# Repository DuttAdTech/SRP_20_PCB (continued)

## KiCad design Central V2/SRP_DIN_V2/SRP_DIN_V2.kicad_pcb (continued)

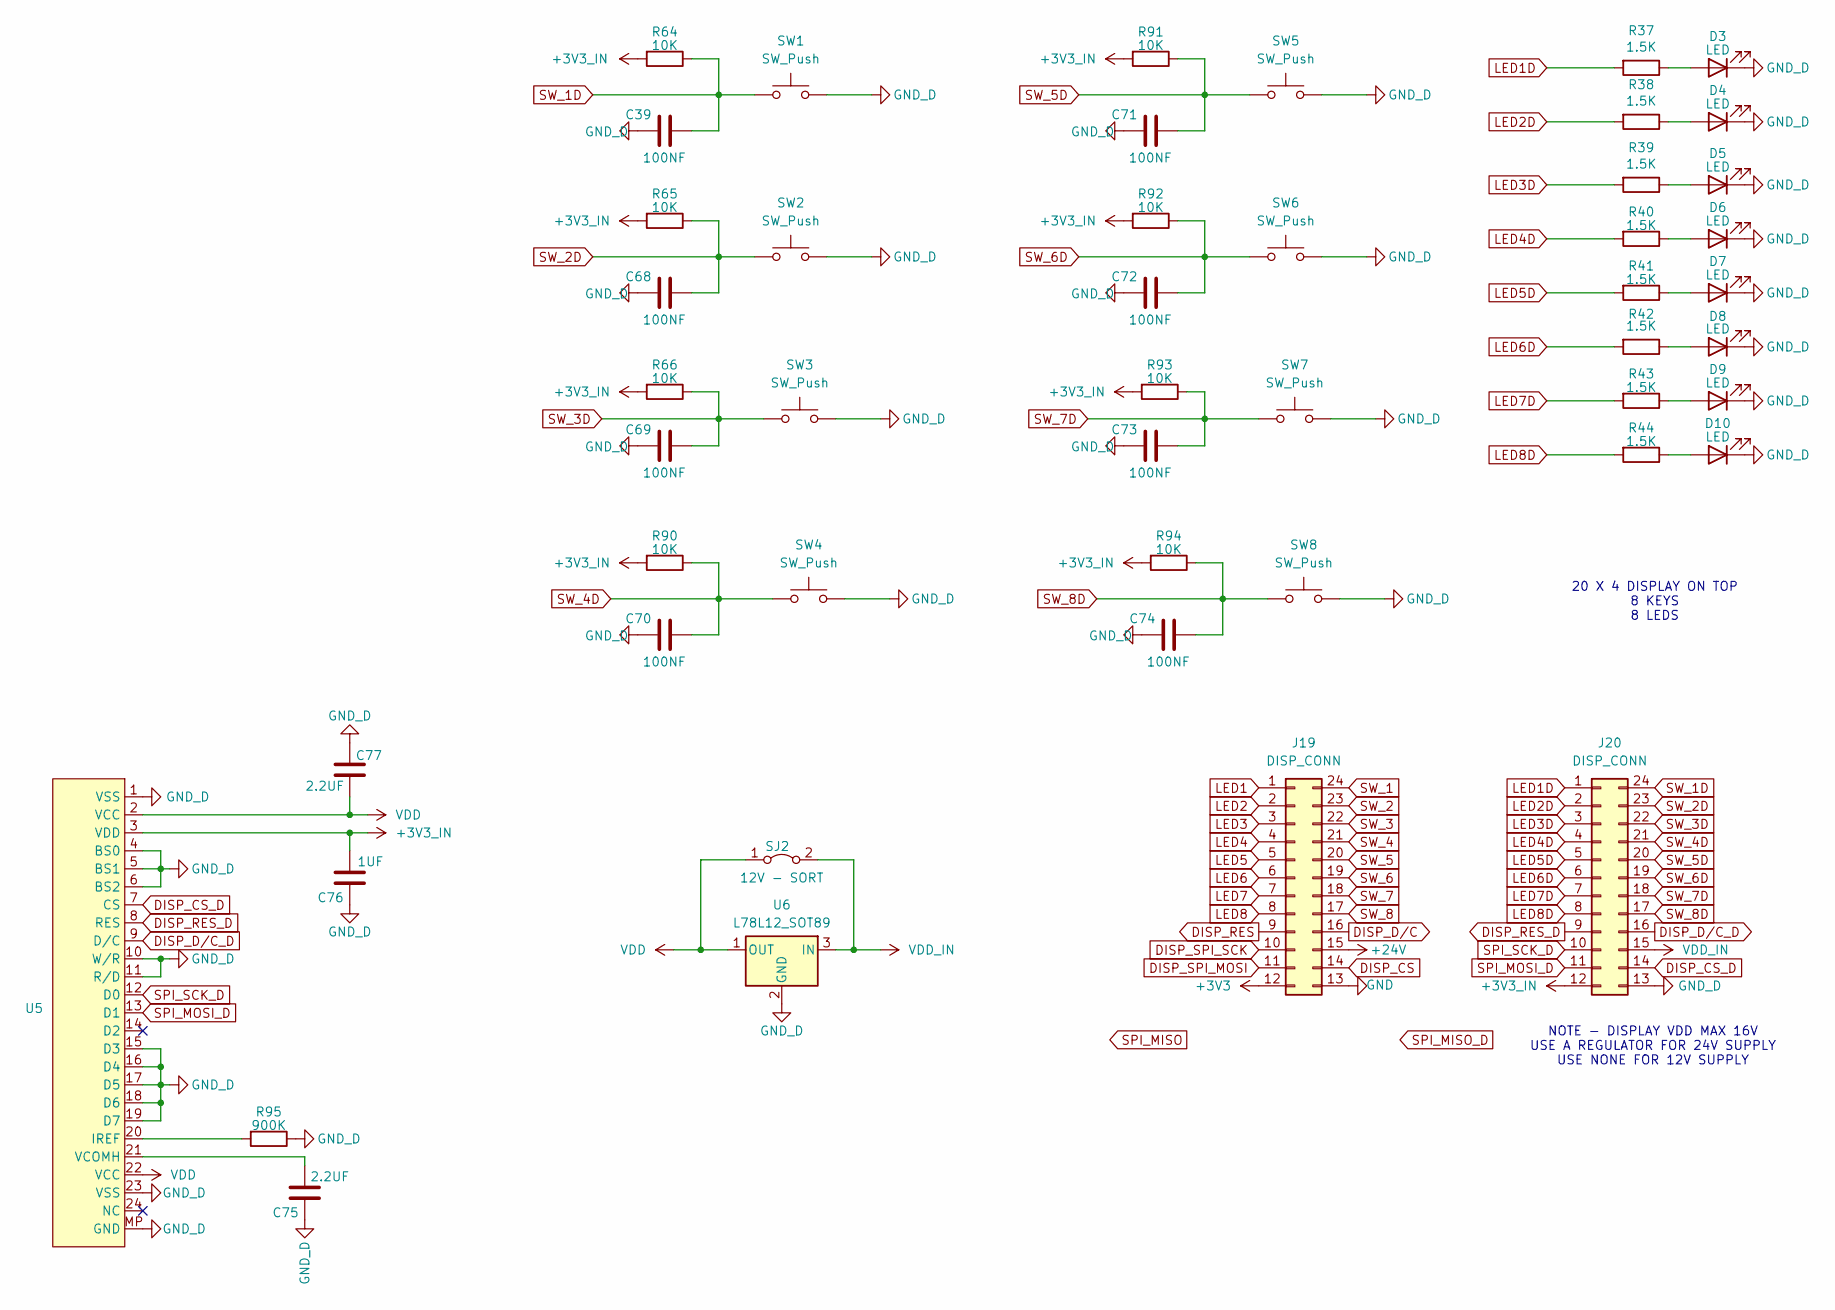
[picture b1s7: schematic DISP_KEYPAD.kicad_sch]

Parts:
C39, C68, C69, C70, C71, C72, C73, C74: 100NF; C_0805_2012Metric
C75, C77: 2.2UF; C_0805_2012Metric
C76: 1UF; C_0805_2012Metric
D3, D4, D5, D6, D7, D8, D9, D10: LED; LED_1206_3216Metric_Pad1.42x1.75mm_HandSolder
J19, J20: DISP_CONN; IDC-Header_2x12_P2.54mm_Vertical
R37, R38, R39, R40, R41, R42, R43, R44: 1.5K; R_0805_2012Metric
R64, R65, R66, R90, R91, R92, R93, R94: 10K; R_0805_2012Metric
R95: 900K; R_0805_2012Metric
SJ2: 12V - SORT; SolderJumper-2_P1.3mm_Open_Pad1.0x1.5mm
SW1, SW2, SW3, SW4, SW5, SW6, SW7, SW8: SW_Push; SW_Push_1P1T_NO_6x6mm_H9.5mm
U5: Hirose_FH12-24S-0.5SH_1x24-1MP_P0.50mm_Horizontal
U6: L78L12_SOT89; SOT-89-3

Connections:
+3V3: J19.12; also elsewhere on the board
+3V3_IN: C76.2, J20.12, R64.2, R65.2, R66.2, R90.2, R91.2, R92.2, R93.2, R94.2, U5.3 (VDD)
+24V: J19.15; also elsewhere on the board
DISP_CS: J19.14; also elsewhere on the board
DISP_CS_D: J20.14, U5.7 (CS)
DISP_D/C: J19.16; also elsewhere on the board
DISP_D/C_D: J20.16, U5.9 (D/C)
DISP_RES: J19.9; also elsewhere on the board
DISP_RES_D: J20.9, U5.8 (RES)
DISP_SPI_MOSI: J19.11; also elsewhere on the board
DISP_SPI_SCK: J19.10; also elsewhere on the board
GND: J19.13; also elsewhere on the board
GND_D: C39.1, C68.1, C69.1, C70.1, C71.1, C72.1, C73.1, C74.1, C75.1, C76.1, C77.1, D3.1 (K), D4.1 (K), D5.1 (K), D6.1 (K), D7.1 (K), D8.1 (K), D9.1 (K), D10.1 (K), J20.13, R95.1, SW1.2, SW2.2, SW3.2, SW4.2, SW5.2, SW6.2, SW7.2, SW8.2, U5.1 (VSS), U5.4 (BS0), U5.5 (BS1), U5.6 (BS2), U5.10 (W/R), U5.11 (R/D), U5.15 (D3), U5.16 (D4), U5.17 (D5), U5.18 (D6), U5.19 (D7), U5.23 (VSS), U5.MP (GND), U6.2 (GND)
LED1: J19.1; also elsewhere on the board
LED1D: J20.1, R37.2
LED2: J19.2; also elsewhere on the board
LED2D: J20.2, R38.2
LED3: J19.3; also elsewhere on the board
LED3D: J20.3, R39.2
LED4: J19.4; also elsewhere on the board
LED4D: J20.4, R40.2
LED5: J19.5; also elsewhere on the board
LED5D: J20.5, R41.2
LED6: J19.6; also elsewhere on the board
LED6D: J20.6, R42.2
LED7: J19.7; also elsewhere on the board
LED7D: J20.7, R43.2
LED8: J19.8; also elsewhere on the board
LED8D: J20.8, R44.2
unnamed: D3.2 (A), R37.1
unnamed: D4.2 (A), R38.1
unnamed: D5.2 (A), R39.1
unnamed: D6.2 (A), R40.1
unnamed: D7.2 (A), R41.1
unnamed: D8.2 (A), R42.1
unnamed: D9.2 (A), R43.1
unnamed: D10.2 (A), R44.1
unnamed: R95.2, U5.20 (IREF)
unnamed: C75.2, U5.21 (VCOMH)
SPI_MOSI_D: J20.11, U5.13 (D1)
SPI_SCK_D: J20.10, U5.12 (D0)
SW_1: J19.24; also elsewhere on the board
SW_1D: C39.2, J20.24, R64.1, SW1.1
SW_2: J19.23; also elsewhere on the board
SW_2D: C68.2, J20.23, R65.1, SW2.1
SW_3: J19.22; also elsewhere on the board
SW_3D: C69.2, J20.22, R66.1, SW3.1
SW_4: J19.21; also elsewhere on the board
SW_4D: C70.2, J20.21, R90.1, SW4.1
SW_5: J19.20; also elsewhere on the board
SW_5D: C71.2, J20.20, R91.1, SW5.1
SW_6: J19.19; also elsewhere on the board
SW_6D: C72.2, J20.19, R92.1, SW6.1
SW_7: J19.18; also elsewhere on the board
SW_7D: C73.2, J20.18, R93.1, SW7.1
SW_8: J19.17; also elsewhere on the board
SW_8D: C74.2, J20.17, R94.1, SW8.1
VDD: C77.2, SJ2.1 (A), U5.2 (VCC), U5.22 (VCC), U6.1 (OUT)
VDD_IN: J20.15, SJ2.2 (B), U6.3 (IN)

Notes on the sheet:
20 X 4 DISPLAY ON TOP 8 KEYS 8 LEDS
NOTE - DISPLAY VDD MAX 16V USE A REGULATOR FOR 24V SUPPLY USE NONE FOR 12V SUPPLY

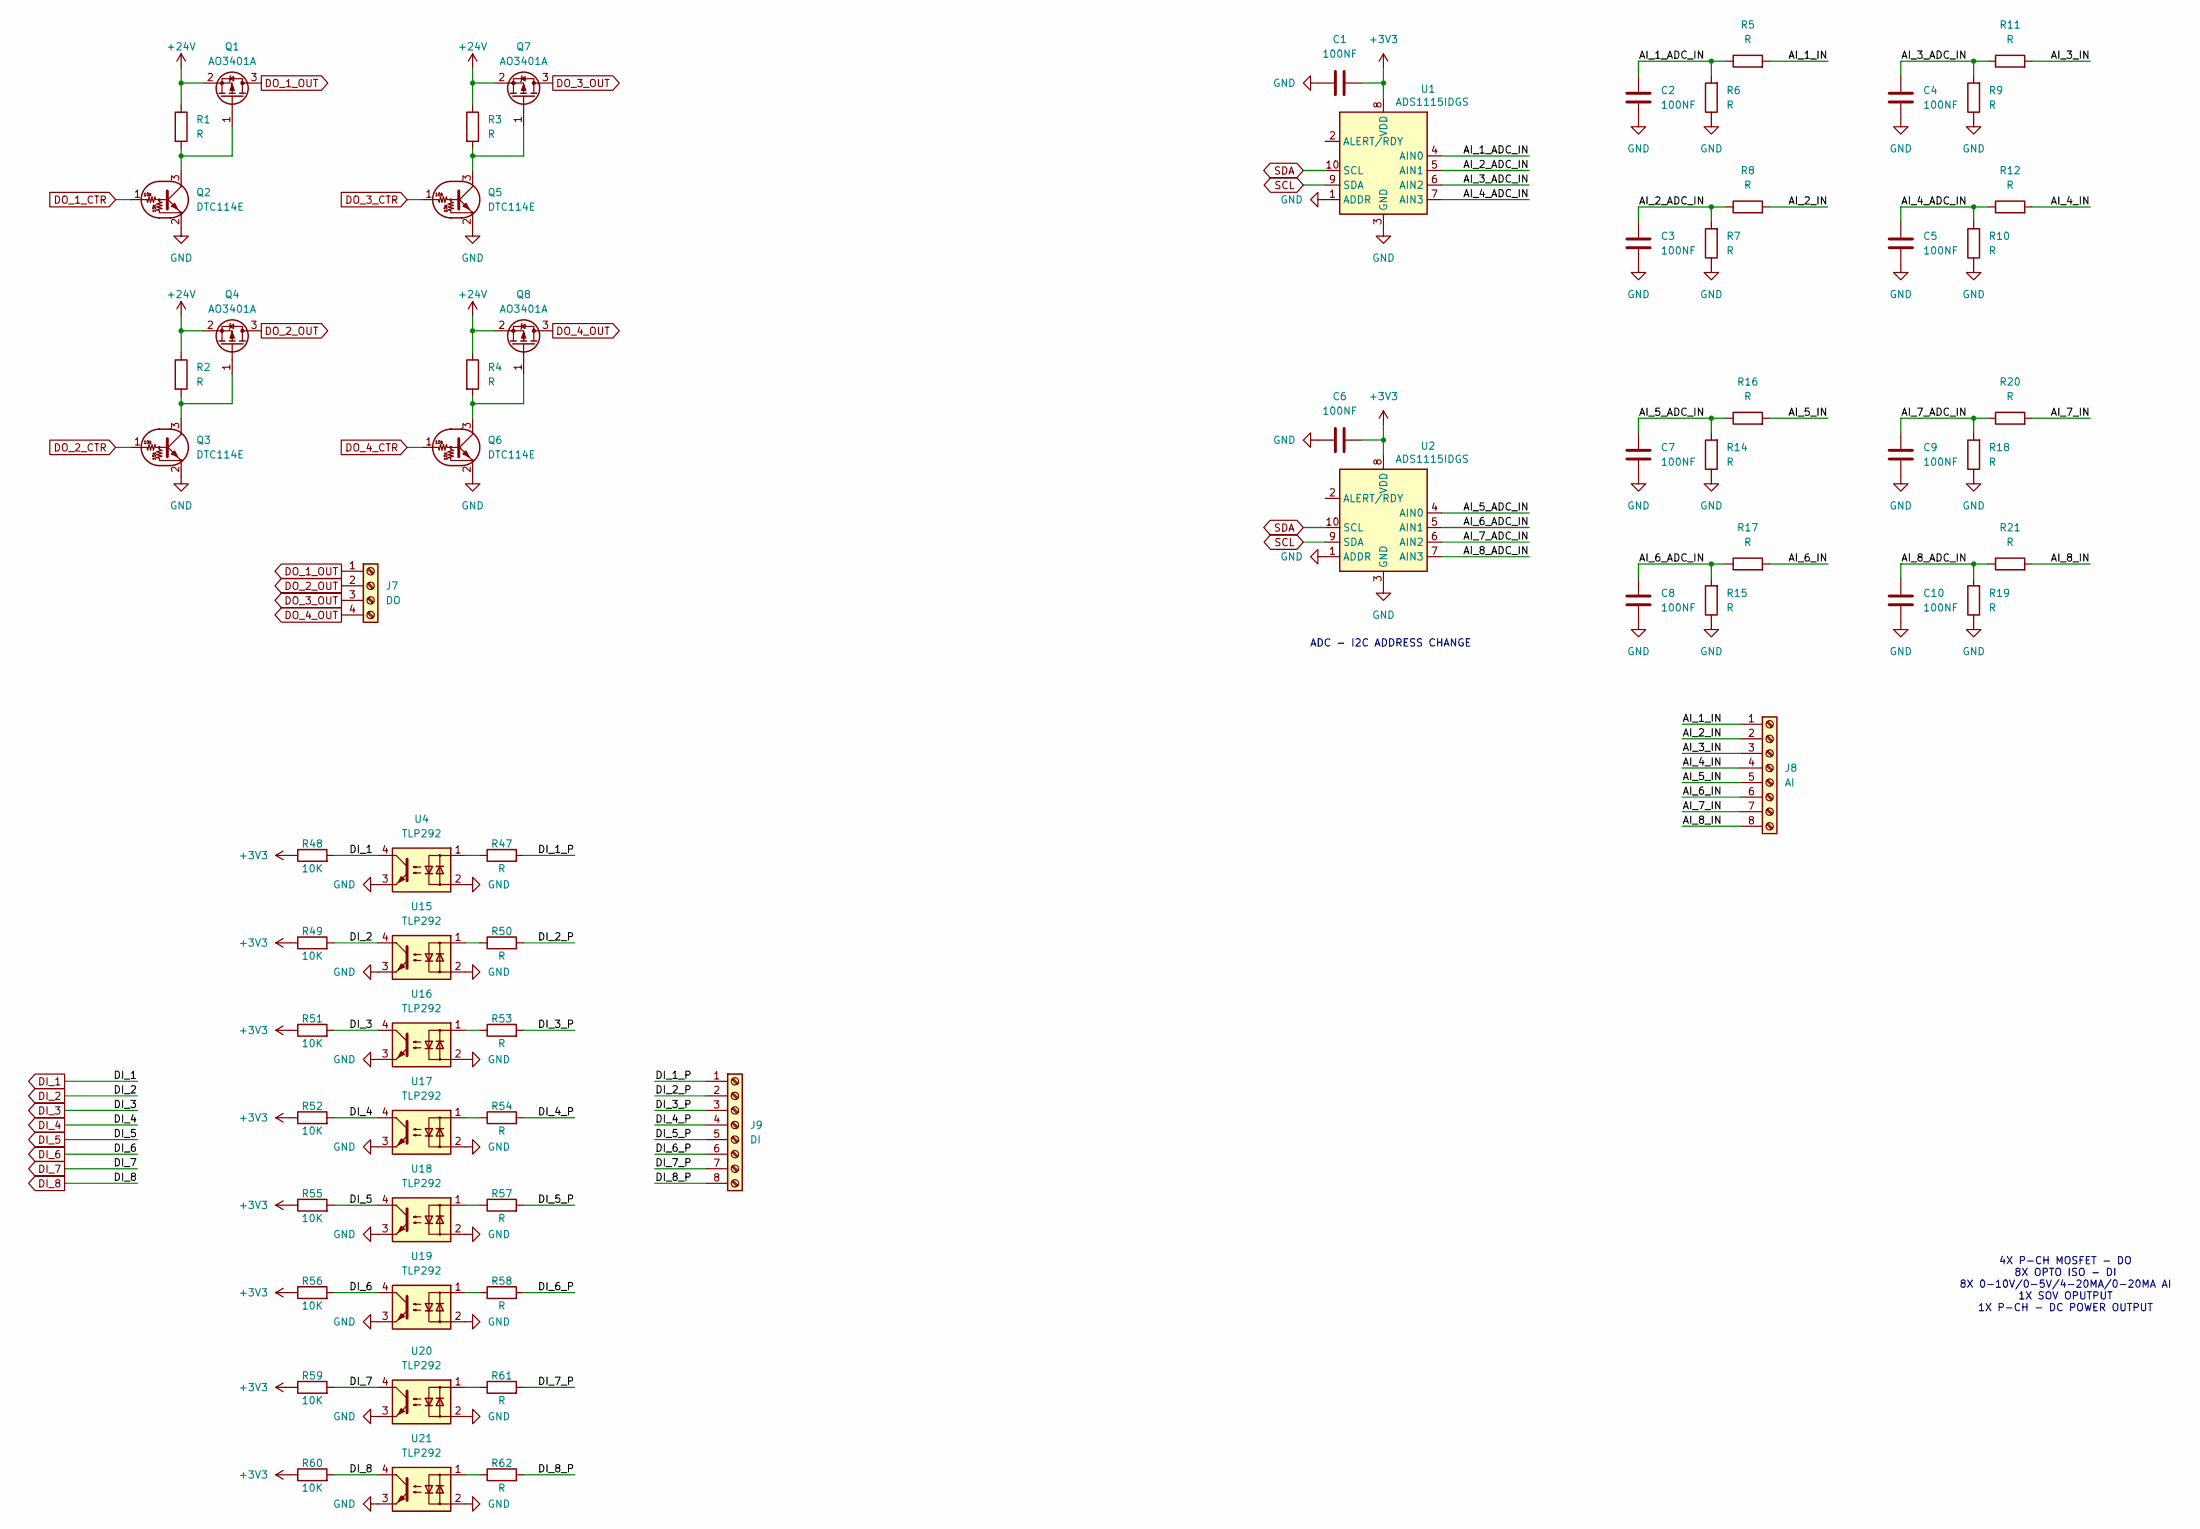
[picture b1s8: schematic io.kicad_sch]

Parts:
C1, C2, C3, C4, C5, C6, C7, C8, C9, C10: 100NF; C_0805_2012Metric
J7: DO; TerminalBlock_Phoenix_MKDS-3-4-5.08_1x04_P5.08mm_Horizontal
J8: AI; TerminalBlock_Phoenix_MKDS-3-8-5.08_1x08_P5.08mm_Horizontal
J9: DI; TerminalBlock_Phoenix_MKDS-3-8-5.08_1x08_P5.08mm_Horizontal
Q1, Q4, Q7, Q8: AO3401A; SOT-23
Q2, Q3, Q5, Q6: DTC114E; SOT-23
R1, R2, R3, R4, R5, R6, R7, R8, R9, R10, R11, R12, R14, R15, R16, R17, R18, R19, R20, R21, R47, R50, R53, R54, R57, R58, R61, R62: R; R_0805_2012Metric
R48, R49, R51, R52, R55, R56, R59, R60: 10K; R_0805_2012Metric
U1, U2: ADS1115IDGS; TSSOP-10_3x3mm_P0.5mm
U4, U15, U16, U17, U18, U19, U20, U21: TLP292; SOIC-4_4.55x2.6mm_P1.27mm

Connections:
+3V3: C1.1, C6.1, R48.1, R49.1, R51.1, R52.1, R55.1, R56.1, R59.1, R60.1, U1.8 (VDD), U2.8 (VDD); also elsewhere on the board
+24V: Q1.2 (S), Q4.2 (S), Q7.2 (S), Q8.2 (S), R1.1, R2.1, R3.1, R4.1; also elsewhere on the board
/IO/AI_1_ADC_IN: C2.1, R5.1, R6.2, U1.4 (AIN0)
/IO/AI_1_IN: J8.1, R5.2
/IO/AI_2_ADC_IN: C3.1, R7.2, R8.1, U1.5 (AIN1)
/IO/AI_2_IN: J8.2, R8.2
/IO/AI_3_ADC_IN: C4.1, R9.2, R11.1, U1.6 (AIN2)
/IO/AI_3_IN: J8.3, R11.2
/IO/AI_4_ADC_IN: C5.1, R10.2, R12.1, U1.7 (AIN3)
/IO/AI_4_IN: J8.4, R12.2
/IO/AI_5_ADC_IN: C7.1, R14.2, R16.1, U2.4 (AIN0)
/IO/AI_5_IN: J8.5, R16.2
/IO/AI_6_ADC_IN: C8.1, R15.2, R17.1, U2.5 (AIN1)
/IO/AI_6_IN: J8.6, R17.2
/IO/AI_7_ADC_IN: C9.1, R18.2, R20.1, U2.6 (AIN2)
/IO/AI_7_IN: J8.7, R20.2
/IO/AI_8_ADC_IN: C10.1, R19.2, R21.1, U2.7 (AIN3)
/IO/AI_8_IN: J8.8, R21.2
/IO/DI_1_P: J9.1, R47.2
/IO/DI_2_P: J9.2, R50.2
/IO/DI_3_P: J9.3, R53.2
/IO/DI_4_P: J9.4, R54.2
/IO/DI_5_P: J9.5, R57.2
/IO/DI_6_P: J9.6, R58.2
/IO/DI_7_P: J9.7, R61.2
/IO/DI_8_P: J9.8, R62.2
DI_1: R48.2, U4.4; also elsewhere on the board
DI_2: R49.2, U15.4; also elsewhere on the board
DI_3: R51.2, U16.4; also elsewhere on the board
DI_4: R52.2, U17.4; also elsewhere on the board
DI_5: R55.2, U18.4; also elsewhere on the board
DI_6: R56.2, U19.4; also elsewhere on the board
DI_7: R59.2, U20.4; also elsewhere on the board
DI_8: R60.2, U21.4; also elsewhere on the board
DO_1_CTR: Q2.1 (B); also elsewhere on the board
DO_1_OUT: J7.1, Q1.3 (D)
DO_2_CTR: Q3.1 (B); also elsewhere on the board
DO_2_OUT: J7.2, Q4.3 (D)
DO_3_CTR: Q5.1 (B); also elsewhere on the board
DO_3_OUT: J7.3, Q7.3 (D)
DO_4_CTR: Q6.1 (B); also elsewhere on the board
DO_4_OUT: J7.4, Q8.3 (D)
GND: C1.2, C2.2, C3.2, C4.2, C5.2, C6.2, C7.2, C8.2, C9.2, C10.2, Q2.2 (E), Q3.2 (E), Q5.2 (E), Q6.2 (E), R6.1, R7.1, R9.1, R10.1, R14.1, R15.1, R18.1, R19.1, U1.1 (ADDR), U1.3 (GND), U2.1 (ADDR), U2.3 (GND), U4.2, U4.3, U15.2, U15.3, U16.2, U16.3, U17.2, U17.3, U18.2, U18.3, U19.2, U19.3, U20.2, U20.3, U21.2, U21.3; also elsewhere on the board
unnamed: Q1.1 (G), Q2.3 (C), R1.2
unnamed: Q3.3 (C), Q4.1 (G), R2.2
unnamed: Q5.3 (C), Q7.1 (G), R3.2
unnamed: Q6.3 (C), Q8.1 (G), R4.2
unnamed: R47.1, U4.1
unnamed: R50.1, U15.1
unnamed: R53.1, U16.1
unnamed: R54.1, U17.1
unnamed: R57.1, U18.1
unnamed: R58.1, U19.1
unnamed: R61.1, U20.1
unnamed: R62.1, U21.1
SCL: U1.9 (SDA), U2.9 (SDA); also elsewhere on the board
SDA: U1.10 (SCL), U2.10 (SCL); also elsewhere on the board

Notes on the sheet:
4X P-CH MOSFET - DO 8X OPTO ISO - DI 8X 0-10V/0-5V/4-20MA/0-20MA AI 1X SOV OPUTPUT 1X P-CH - DC POWER OUTPUT
ADC - I2C ADDRESS CHANGE

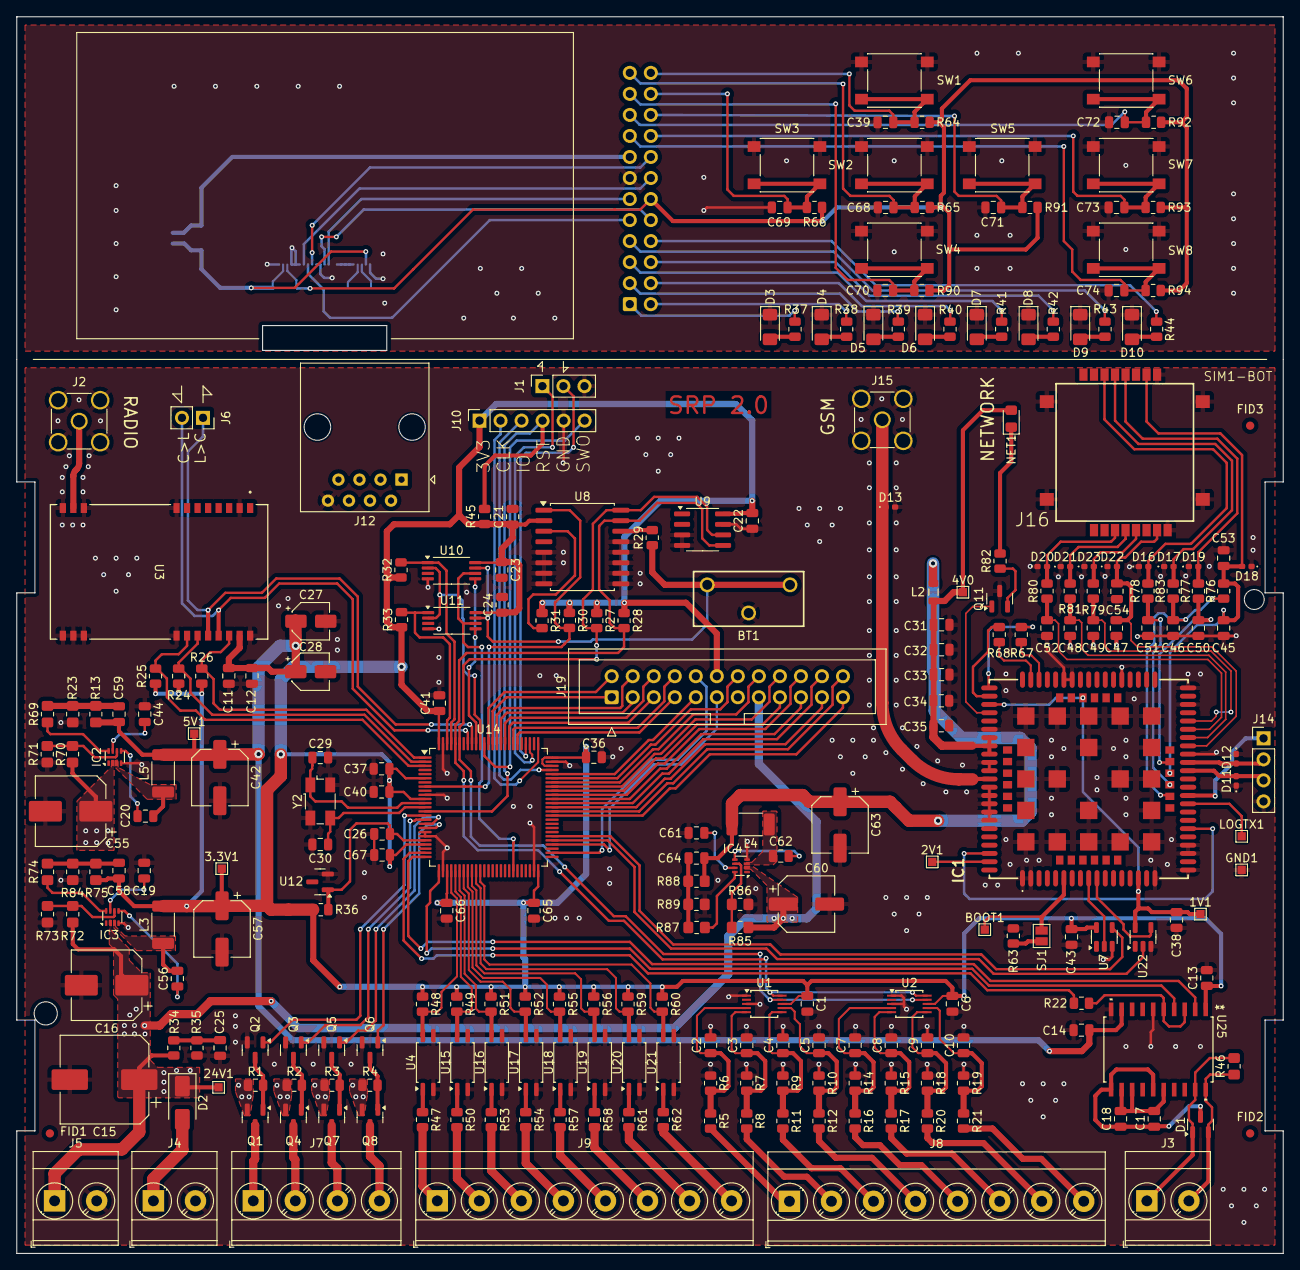
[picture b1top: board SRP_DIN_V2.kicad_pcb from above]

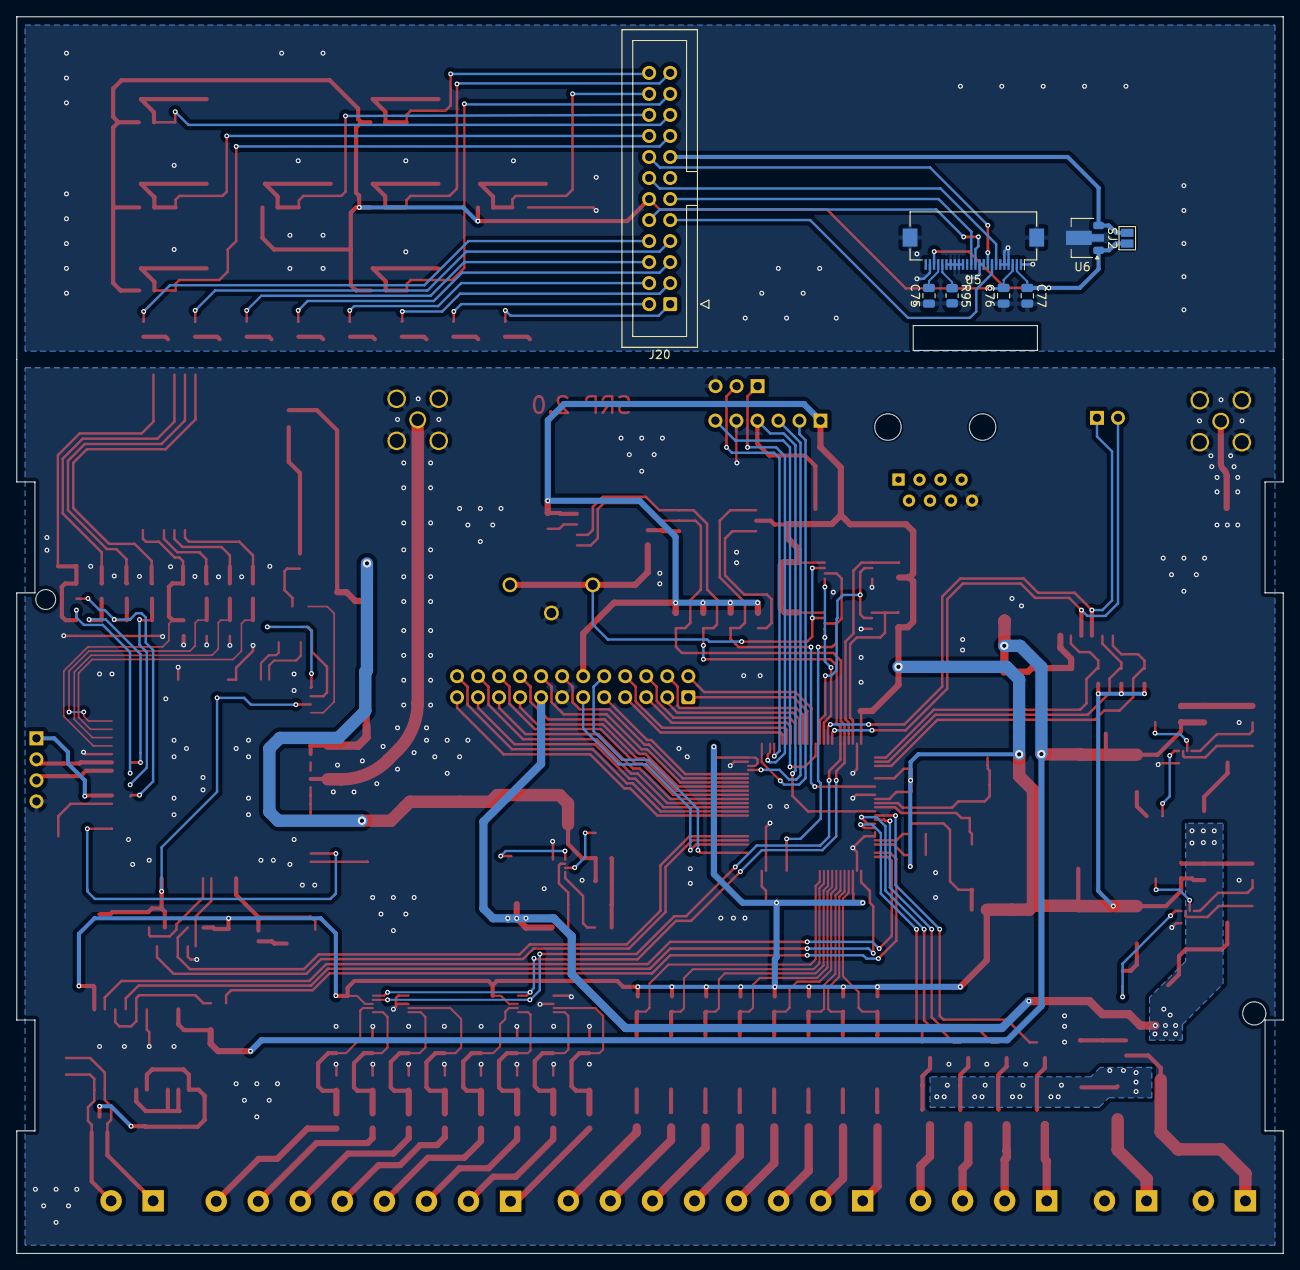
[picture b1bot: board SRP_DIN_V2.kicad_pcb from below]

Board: 2 copper layers, 153.0 x 149.4 mm, 273 parts (8 on the bottom side), 203 nets.

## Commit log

2025-04-23 Initial Project Added
2025-04-23 Changed to V2
